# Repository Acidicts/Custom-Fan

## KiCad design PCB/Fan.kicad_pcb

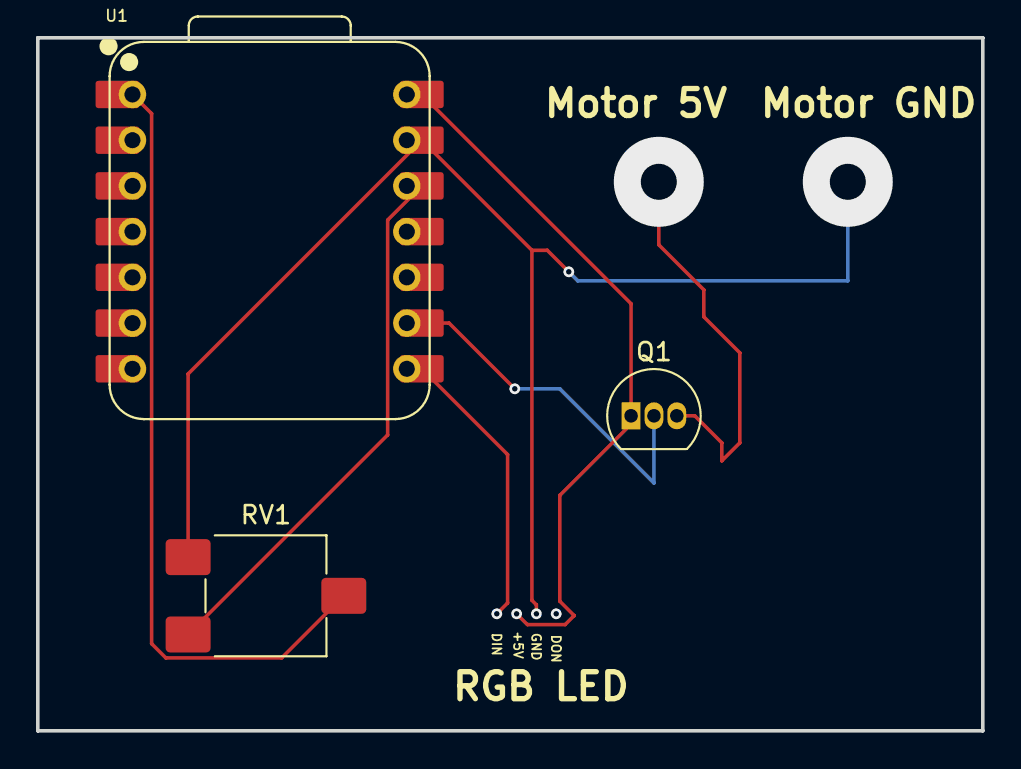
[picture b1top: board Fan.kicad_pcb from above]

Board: 2 copper layers, 52.5 x 38.5 mm, 3 parts (0 on the bottom side), 5 nets.

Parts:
Q1: BC517; TO-92_Inline
RV1: R_Potentiometer; Potentiometer_ACP_CA6-VSMD_Vertical
U1: XIAO-RP2040-DIP

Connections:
+3.3V: RV1.1, U1.12 (3V3)
+5V: Q1.1 (C), U1.14 (VBUS)
GND: RV1.3, U1.13 (GND)
unnamed: Q1.2 (B), U1.9 (GPIO2/SCK)
unnamed: RV1.2, U1.1 (GPIO26/ADC0/A0)

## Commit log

2025-06-30 Uploaded PCB and SCH
2025-06-30 Rename Screenshot 2025-06-30 164617.png to pcb.png
2025-06-30 Rename Schematic/Screenshot 2025-06-30 164304.png to sch.png
2025-06-30 Moved sch.png to Schematic/sch.png
2025-06-30 Added BOM
    - Added Bill of Materials
